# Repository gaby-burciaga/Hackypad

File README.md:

# Gabriel's CREATION

Finally my creation is ready :)

## Hackpad

## Bottom case

## Plate

## Schematic

## PCB

## Challenges

This was my first time designing a PCB, it was really fun and exciting to do, i felt like i was really designing something that i could really use. Using KMK was a little difficult to use, i struggled trying to set the correct pins for my keys. Trying to understand how to layout the OLED connector (GND VCC SDA SCL) was a real nightmare, but at the end, it was a really rewarding experience.

## BOM

* 4x Cherry MX Switches
* 1x SK6812 MINI Leds
* 1x XIAO RP2040
* 4x Blank DSA Keycaps
* 4x M3x16 Bolt
* 4x M3 Heatset
* 1x 0.91 OLED Display
* 1x EC11 Rotary encoder

others: 

* KMK Firmware
* Bottom case.STEP
* Plate.STEP

I used Solidworks to design the case, KiCAD for the PCB, and vscode to write the firmware.

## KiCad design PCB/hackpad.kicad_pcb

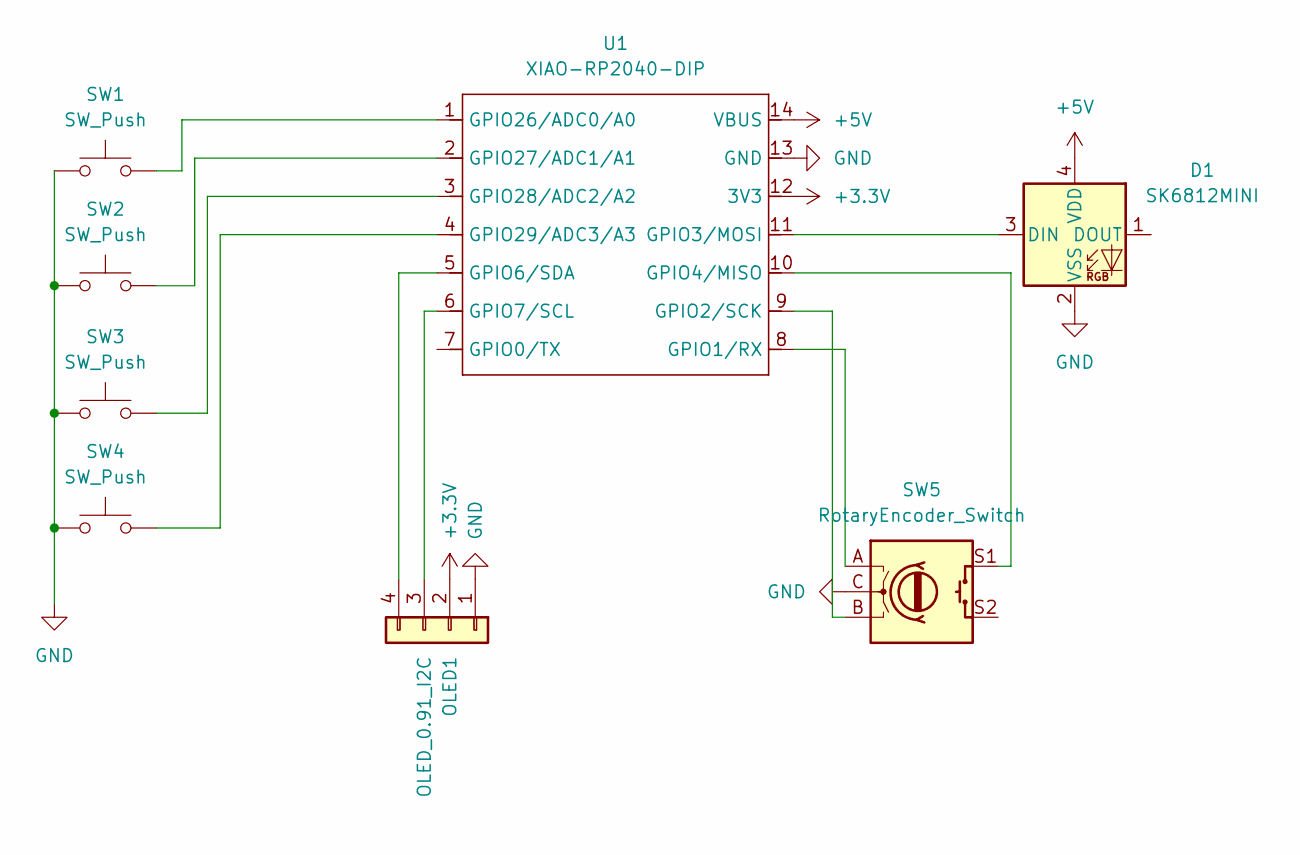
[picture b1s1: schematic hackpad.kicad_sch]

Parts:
D1: SK6812MINI; LED_SK6812MINI_PLCC4_3.5x3.5mm_P1.75mm
OLED1: OLED_0.91_I2C; PinHeader_1x04_P2.54mm_Vertical
SW1, SW2, SW3, SW4: SW_Push; SW_Cherry_MX_1.00u_PCB
SW5: RotaryEncoder_Switch; RotaryEncoder_Alps_EC11E-Switch_Vertical_H20mm
U1: XIAO-RP2040-DIP

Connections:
+3.3V: OLED1.2 (VCC), U1.12 (3V3)
+5V: D1.4 (VDD), U1.14 (VBUS)
GND: D1.2 (VSS), OLED1.1 (GND), SW1.1, SW2.1, SW3.1, SW4.1, SW5.C, U1.13 (GND)
unnamed: D1.3 (DIN), U1.11 (GPIO3/MOSI)
unnamed: OLED1.3 (SCL), U1.6 (GPIO7/SCL)
unnamed: OLED1.4 (SDA), U1.5 (GPIO6/SDA)
unnamed: SW5.A, U1.8 (GPIO1/RX)
unnamed: SW5.B, U1.9 (GPIO2/SCK)
unnamed: SW5.S1, U1.10 (GPIO4/MISO)
unnamed: SW1.2, U1.1 (GPIO26/ADC0/A0)
unnamed: SW2.2, U1.2 (GPIO27/ADC1/A1)
unnamed: SW3.2, U1.3 (GPIO28/ADC2/A2)
unnamed: SW4.2, U1.4 (GPIO29/ADC3/A3)

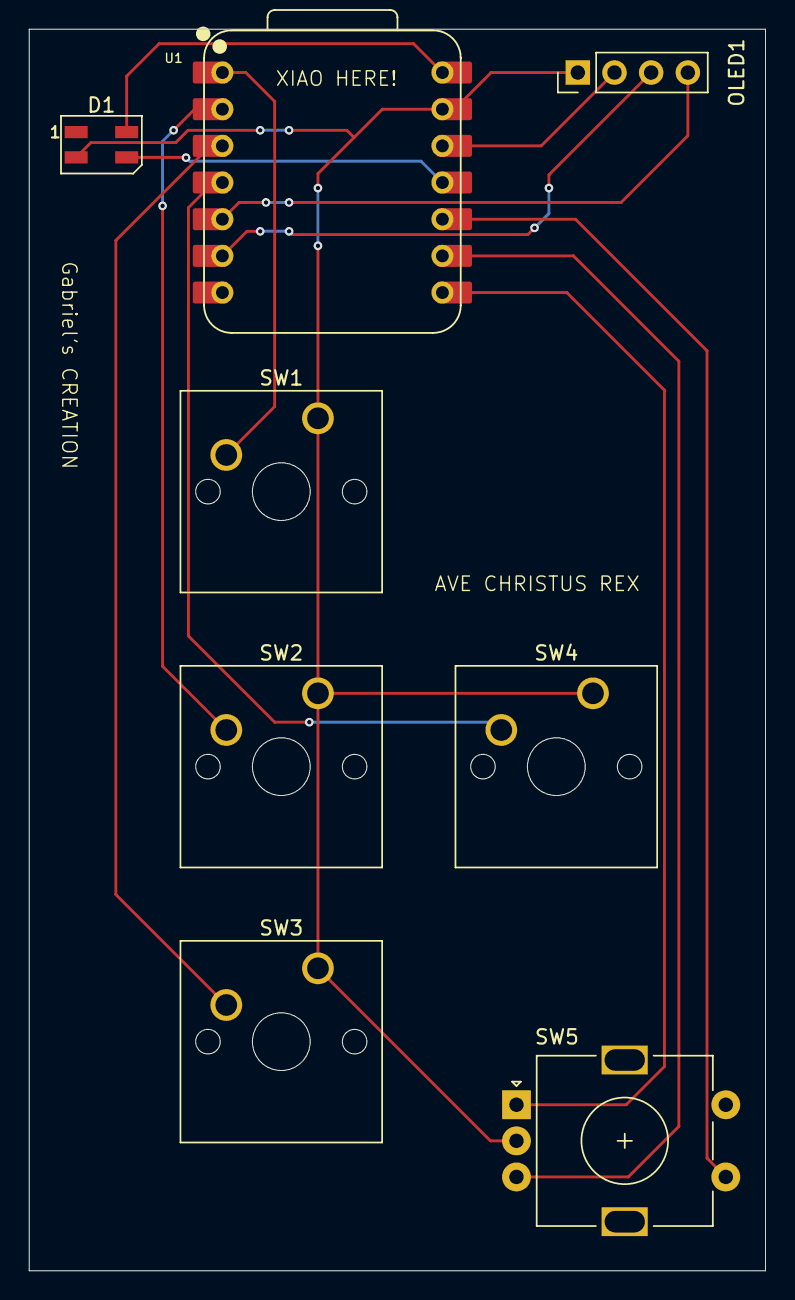
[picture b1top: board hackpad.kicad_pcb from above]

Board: 2 copper layers, 51.0 x 86.0 mm, 8 parts (0 on the bottom side), 13 nets.

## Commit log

2025-12-27 Add README
2025-12-27 Add an smile
2025-12-27 Update BOM
